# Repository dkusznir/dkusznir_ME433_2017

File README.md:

# dkusznir_ME433_2017
ME 433 - Advanced Mechatronics

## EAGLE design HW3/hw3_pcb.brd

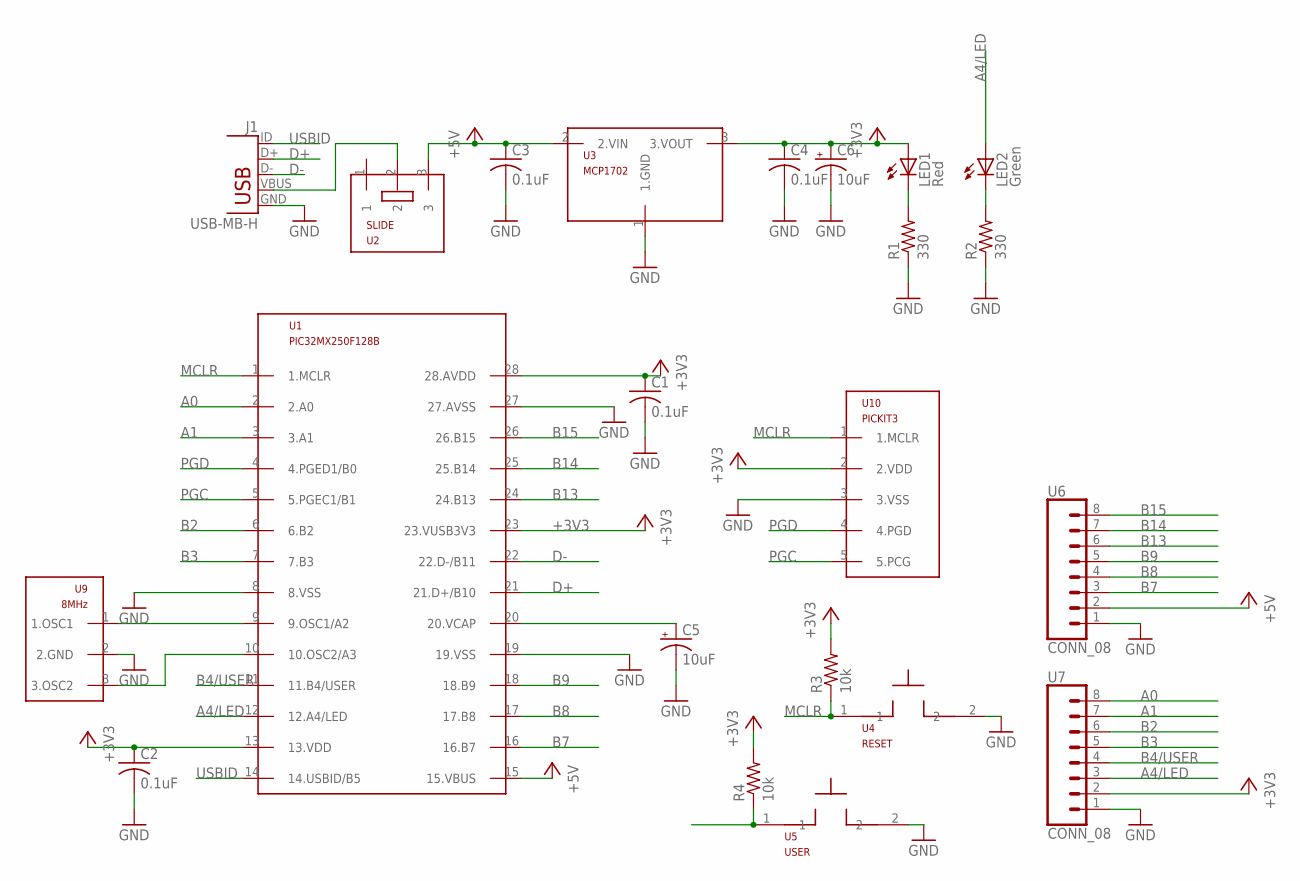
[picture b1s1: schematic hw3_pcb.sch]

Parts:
C1, C2, C3, C4: 0.1uF; C025-025X050
C5, C6: 10uF; B45181B
J1: USB-MB-H
LED1: Red; LED3MM
LED2: Green; LED3MM
R1, R2: 330; 0207/10
R3, R4: 10k; 0207/10
U1: PIC32MX250F128B; DIL28-3
U2: SLIDE
U3: MCP1702; TO92
U4: RESET; PB
U5: USER; PB
U6, U7: CONN_08; 1X08
U9: 8MHz; OSC
U10: PICKIT3; 1X05

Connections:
+3V3: C1.1, C2.1, C4.1, C6.+, LED1.A, R3.2, R4.2, U1.13 (13.VDD), U1.23 (23.VUSB3V3), U1.28 (28.AVDD), U3.3 (3.VOUT), U7.2, U10.2 (2.VDD)
+5V: C3.1, U1.15 (15.VBUS), U2.3, U3.2 (2.VIN), U6.2
A0: U1.2 (2.A0), U7.8
A1: U1.3 (3.A1), U7.7
A4/LED: LED2.A, U1.12 (12.A4/LED), U7.3
B2: U1.6 (6.B2), U7.6
B3: U1.7 (7.B3), U7.5
B4/USER: R4.1, U1.11 (11.B4/USER), U5.1, U7.4
B7: U1.16 (16.B7), U6.3
B8: U1.17 (17.B8), U6.4
B9: U1.18 (18.B9), U6.5
B13: U1.24 (24.B13), U6.6
B14: U1.25 (25.B14), U6.7
B15: U1.26 (26.B15), U6.8
D+: J1.D+, U1.21 (21.D+/B10)
D-: J1.D-, U1.22 (22.D-/B11)
GND: C1.2, C2.2, C3.2, C4.2, C5.-, C6.-, J1.GND, R1.1, R2.1, U1.8 (8.VSS), U1.19 (19.VSS), U1.27 (27.AVSS), U3.1 (1.GND), U4.2, U5.2, U6.1, U7.1, U9.2 (2.GND), U10.3 (3.VSS)
MCLR: R3.1, U1.1 (1.MCLR), U4.1, U10.1 (1.MCLR)
unnamed: J1.VBUS, U2.2
unnamed: LED2.K (C), R2.2
unnamed: LED1.K (C), R1.2
OSC1/A2: U1.9 (9.OSC1/A2), U9.1 (1.OSC1)
OSC2/A3: U1.10 (10.OSC2/A3), U9.3 (3.OSC2)
PGC: U1.5 (5.PGEC1/B1), U10.5 (5.PCG)
PGD: U1.4 (4.PGED1/B0), U10.4 (4.PGD)
USBID: J1.ID, U1.14 (14.USBID/B5)
VCAP: C5.+, U1.20 (20.VCAP)

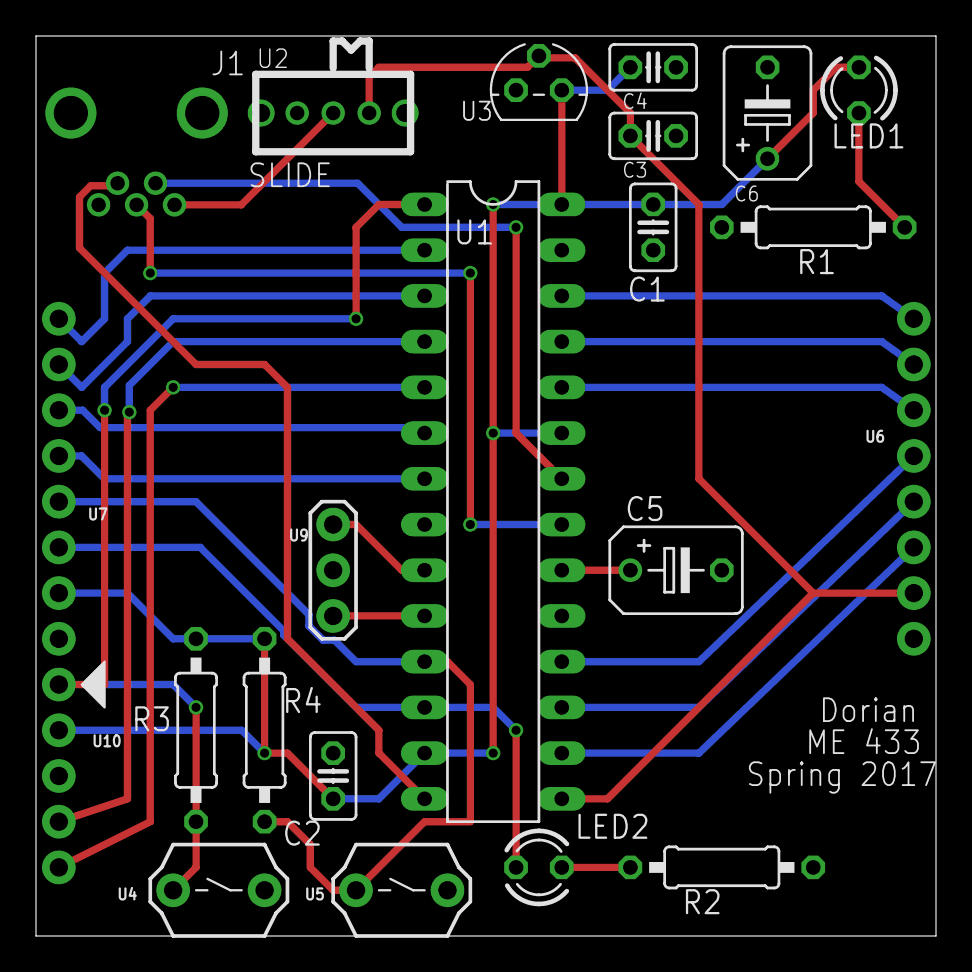
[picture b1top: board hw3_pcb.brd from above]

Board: 2 copper layers, 50.0 x 50.0 mm, 22 parts (0 on the bottom side), 27 nets.

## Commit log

2017-03-30 Part 2 - screenshot of oscillations
2017-03-30 Part 2 - screenshot of clean 3.3V
2017-03-30 Part 1 - circuit diagram
2017-03-30 Part 6 - breadboard
2017-03-30 Programming the PIC - created empty C file in MPLABX
2017-03-30 Programming - final code working
2017-04-02 Creating HW2 folder
2017-04-03 Followed EAGLElibraries tutorial to create voltage regulator
2017-04-03 Finished creating custom library for schematic
2017-04-03 Finished schematic
2017-04-03 Removing .epf file
2017-04-03 Added PDF of schematic
2017-04-05 Missed a ground connection on the schematic. Fixed it.
2017-04-05 HW3 created. Almost done with .brd configuration
2017-04-05 Added copper plane for GND connections
2017-04-05 UI board updates. Still working on this.
2017-04-05 Error checking complete. PCD complete. Had to modify USB pin spacing so I updated the library and schematic accordingly
2017-04-05 Added picture of final pcb design.
2017-04-05 Adding second pic with GND plane displayed
2017-04-05 Adding gerber files and Seeed cam file
2017-04-11 Finished schematic. Uploading JPEG.
2017-04-11 Circuit finished. Uploading JPEG of completed circuit.
2017-04-11 Had to move nscope on my circuit. Uploading a better image of the completed designed.
2017-04-11 Creating HW4 project in MPLAB IDE.
2017-04-11 Created SPI files
2017-04-11 Done working on SPI.
2017-04-12 Created HW5 folder and added circuit diagram for MCP23008.
2017-04-12 Adding picture of completed circuit.
2017-04-12 Had wrong resistor value for push button (330 ohm, should have been 10k ohm). Made change in diagram.
2017-04-12 Created HW5 project in mplabIDE and added i2c_master files from ME433 git repo.
2017-04-12 Updated I2C1 to I2C2 and calculated I2C2BRG value.
2017-04-12 Added main file. Copied from HW1.
2017-04-12 Added expander functions.
2017-04-12 Working on expander functions.
2017-04-13 LED completed.
2017-04-13 Forgot to add pull up resistors to the circuit diagram. Modified it accordingly.
2017-04-17 Added ILI9163 files from class repo.
2017-04-17 Circuit completed.
2017-04-17 Added main function.
2017-04-18 Finished display functions. Working on main.
2017-04-18 Basically working. Display doesn't reset correctly when it gets to 100, but other than that it works.
2017-04-24 Creating HW7 directory
2017-04-27 finished HW7
2017-04-27 Changed bar color to something better.
2017-04-27 Created HW8 project
2017-04-27 HW1 code working with Harmony.
2017-04-27 Modified HW1 code to work better (brighter LED).
2017-04-27 Added IMU files.
2017-04-27 Somewhat working. IMU is now acting weird.
2017-04-27 Fixed problem. Working now.
2017-04-27 Cleaned up code a bit.
2017-04-27 Cleaning up code.
2017-05-01 Created HW9
2017-05-01 Made a mistake in setup. Removing directory
2017-05-01 Recreated HW9 directory and Harmony project.
2017-05-01 Added USB code and confirmed working (number incrementing at 5HZ in serial terminal).
2017-05-01 Added i2c code to HW9
2017-05-01 Added IMU code to HW9.
2017-05-01 Adding IMU code to app.c
2017-05-01 HW9 done.
2017-05-03 Updated Makefile.
2017-05-03 Created HW10 project. Added HW9 code and confirmed that it is working properly.
2017-05-03 Initialized filter variables. Working on filters now.
2017-05-05 Added MAF & IIR. Almost done with FIR.
2017-05-05 Filters working. Matlab not working.
2017-05-05 Got it working with python.
2017-05-05 Done with HW10. Fixed FIR and got it to plot using python.
2017-05-05 Created HW11.
2017-05-05 Added files from usb/hid directory.
2017-05-05 Finished HID tutorial and added IMU code from HW10.
2017-05-06 Done with HW11.
2017-05-06 Started HW12. Finished 'Hello World' tutorial.
2017-05-06 Finished HW12.
2017-05-07 Checking out Android Studio. Added an increase and decrease button to change the Seek Bar.
2017-05-14 Created HW13.
2017-05-14 Camera app working.
2017-05-14 Color recognition and drawing lines over green objects working.
2017-05-14 Added some comments to my code.
2017-05-14 Added slider. Increased number of rows skipped in for loop to improve performance.
2017-05-14 SeekBar done. TextView displaying SeekBar status done. Just need to hook it up to thresh value in function onSurfaceTextureUpdated
2017-05-14 Done with HW13.
2017-05-14 Removing deleted files.
2017-05-14 Created HW14.
2017-05-14 Replicated CDC tutorial again and it is working.
2017-05-14 Finished editing CDC code to only show number if /n or /r. Now starting Android section.
2017-05-14 Created androidUSB project.
2017-05-14 Tested android app with sliders and text views updating correctly.
2017-05-14 Added USB code to Android app.
2017-05-14 Done with HW14.
2017-05-19 Finished box drawing.
2017-05-19 Finished wheel drawing.
2017-05-19 Made some minor improvements.
2017-05-19 Wrong wheel picture. Added correct one.
2017-05-19 Added wheel stl file.
2017-05-22 Adding better pictures of the box drawing.
2017-05-22 3D printed wheel.
2017-05-29 Working on HW18.
2017-05-30 Starting HW19 - camera app to detect center of path.
2017-05-30 git issues
2017-05-31 Looking for gray path. Implemented that in code. Still working on finding the center of mass.
2017-05-31 Still working on center of mass.
2017-05-31 Created Harmony project for HW18.
2017-05-31 Set up timer2.
2017-06-01 Got motor working with H bridge.
2017-06-01 Got com working better.
2017-06-01 Added com printout to app.
2017-06-02 Working on final project
2017-06-02 Added Android code from HW19. Working on connectivity.
2017-06-02 Modifying PIC code. Added USB connectivity (Android <-> PIC).
2017-06-02 Changed default threshold value to 20.
2017-06-03 Working on final. Issues with android app crashing when combining USB and camera functionalities.
2017-06-03 Fixed crash issue. Now USB doesn't send data.
2017-06-04 Still having issues with Android.
2017-06-04 Made some changes to PIC code for testing later.
2017-06-04 Another small change.
2017-06-06 Trying something new.
2017-06-07 basically working.
2017-06-07 Finished HW17.
2017-06-07 Added pics of the robot.
2017-06-07 Added Vive position sensor code.
